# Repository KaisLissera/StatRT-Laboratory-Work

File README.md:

# Stat_RT_Laboratory_Work
 Updating of equipment for laboratory work on statistical radiotechnics

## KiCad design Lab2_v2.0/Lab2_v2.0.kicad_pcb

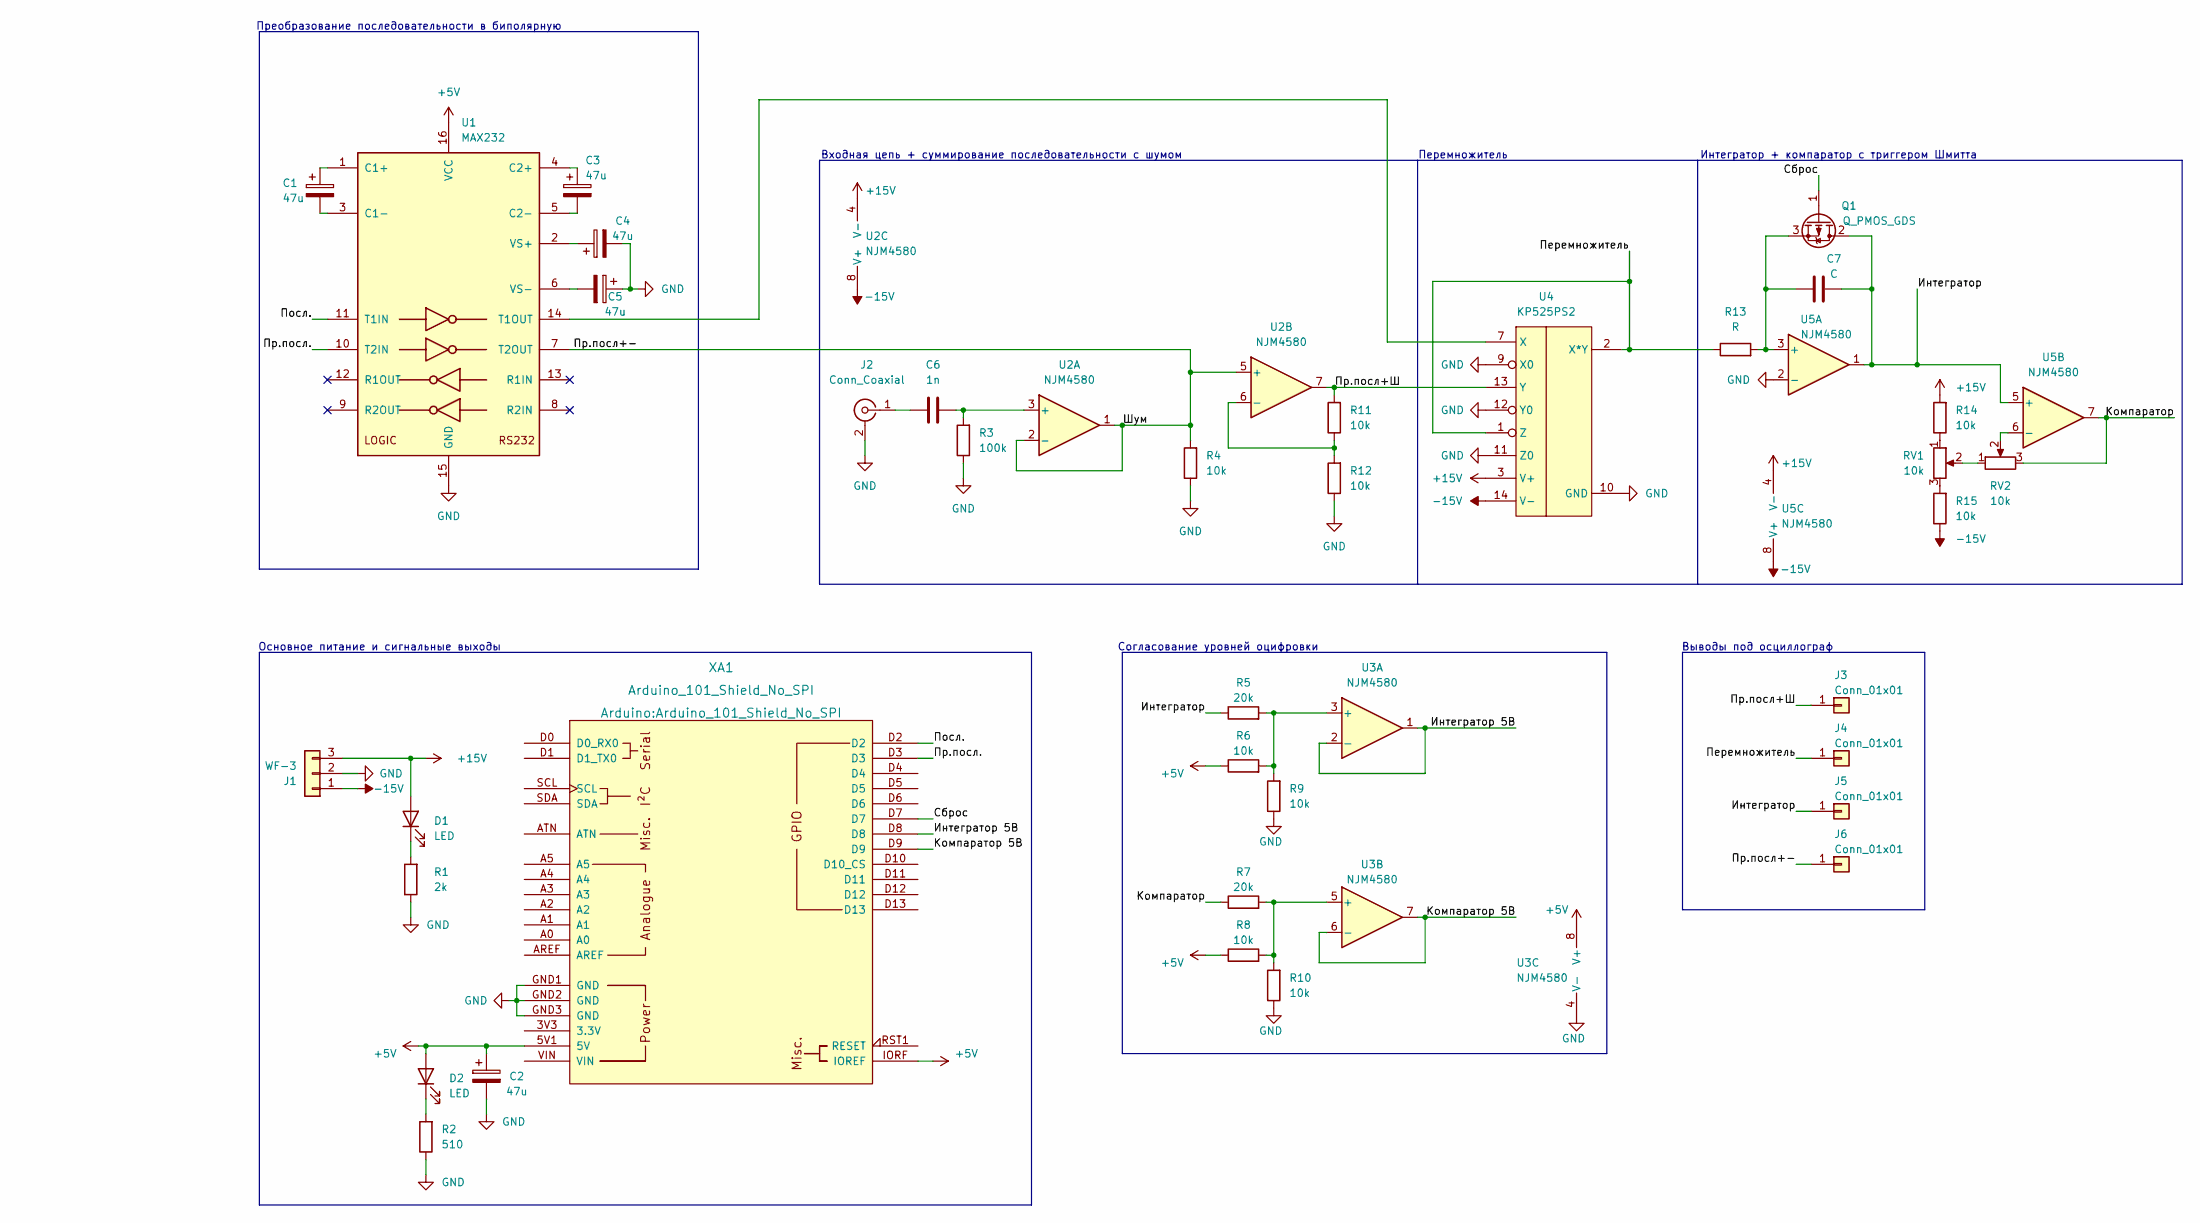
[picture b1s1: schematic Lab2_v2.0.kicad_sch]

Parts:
C1, C2, C3, C4, C5: 47u; CP_EIA-3216-18_Kemet-A_Pad1.58x1.35mm_HandSolder
C6: 1n; C_0603_1608Metric_Pad1.08x0.95mm_HandSolder
C7: C; C_0603_1608Metric_Pad1.08x0.95mm_HandSolder
D1, D2: LED; LED_0603_1608Metric_Pad1.05x0.95mm_HandSolder
J1: WF-3; PinHeader_1x03_P2.54mm_Vertical
J2: Conn_Coaxial; BNC_TEConnectivity_1478204_Vertical
J3, J4, J5, J6: Conn_01x01; PinHeader_1x01_P2.54mm_Vertical
Q1: Q_PMOS_GDS; SOT-23
R1: 2k; R_0603_1608Metric_Pad0.98x0.95mm_HandSolder
R2: 510; R_0603_1608Metric_Pad0.98x0.95mm_HandSolder
R3: 100k; R_0603_1608Metric_Pad0.98x0.95mm_HandSolder
R4, R6, R8, R9, R10, R11, R12, R14, R15: 10k; R_0603_1608Metric_Pad0.98x0.95mm_HandSolder
R5, R7: 20k; R_0603_1608Metric_Pad0.98x0.95mm_HandSolder
R13: R; R_0603_1608Metric_Pad0.98x0.95mm_HandSolder
RV1, RV2: 10k; Potentiometer_Bourns_3266W_Vertical
U1: MAX232; DIP-16_W7.62mm
U2, U3, U5: NJM4580; SOIC-8_3.9x4.9mm_P1.27mm
U4: KP525PS2; DIP-14_W7.62mm
XA1: Arduino_101_Shield_No_SPI

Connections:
+5V: C2.1, D2.2 (A), R6.1, R8.1, U1.16 (VCC), U3.8 (V+), XA1.5V1 (5V), XA1.IORF (IOREF)
+15V: D1.2 (A), J1.3, R14.2, U2.4 (V-), U4.3 (V+), U5.4 (V-)
-15V: J1.1, R15.1, U2.8 (V+), U4.14 (V-), U5.8 (V+)
/Интегратор: C7.2, J5.1, Q1.2 (D), R5.1, U5.1, U5.5 (+)
/Интегратор 5В: U3.1, U3.2 (-), XA1.D8
/Компаратор: R7.1, RV2.3, U5.7
/Компаратор 5В: U3.6 (-), U3.7, XA1.D9
/Перемножитель: J4.1, R13.1, U4.1 (Z), U4.2 (X*Y)
/Посл.: U1.11 (T1IN), XA1.D2
/Пр.посл+-: J6.1, R4.2, U1.7 (T2OUT), U2.1, U2.2 (-), U2.5 (+)
/Пр.посл+Ш: J3.1, R11.2, U2.7, U4.13 (Y)
/Пр.посл.: U1.10 (T2IN), XA1.D3
/Сброс: Q1.1 (G), XA1.D7
GND: C2.2, C4.2, C5.1, J1.2, J2.2 (Ext), R1.1, R2.1, R3.1, R4.1, R9.1, R10.1, R12.1, U1.15 (GND), U3.4 (V-), U4.6, U4.9 (X0), U4.10 (GND), U4.11 (Z0), U4.12 (Y0), U5.2 (-), XA1.GND1 (GND), XA1.GND2 (GND), XA1.GND3 (GND)
unnamed: C1.1, U1.1 (C1+)
unnamed: C1.2, U1.3 (C1-)
unnamed: C3.1, U1.4 (C2+)
unnamed: C3.2, U1.5 (C2-)
unnamed: C4.1, U1.2 (VS+)
unnamed: C5.2, U1.6 (VS-)
unnamed: C6.1, J2.1 (In)
unnamed: C6.2, R3.2, U2.3 (+)
unnamed: C7.1, Q1.3 (S), R13.2, U5.3 (+)
unnamed: D1.1 (K), R1.2
unnamed: D2.1 (K), R2.2
unnamed: R5.2, R6.2, R9.2, U3.3 (+)
unnamed: R7.2, R8.2, R10.2, U3.5 (+)
unnamed: R11.1, R12.2, U2.6 (-)
unnamed: R14.1, RV1.1
unnamed: R15.2, RV1.3
unnamed: RV1.2, RV2.1
unnamed: RV2.2, U5.6 (-)
unnamed: U1.14 (T1OUT), U4.7 (X)

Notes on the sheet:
Входная цепь + суммирование последовательности с шумом
Интегратор + компаратор с триггером Шмитта
Преобразование последовательности в биполярную
Основное питание и сигнальные выходы
Выводы под осциллограф
Согласование уровней оцифровки
Перемножитель

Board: 2 copper layers, 39 parts (0 on the bottom side), 33 nets, no tracks yet.

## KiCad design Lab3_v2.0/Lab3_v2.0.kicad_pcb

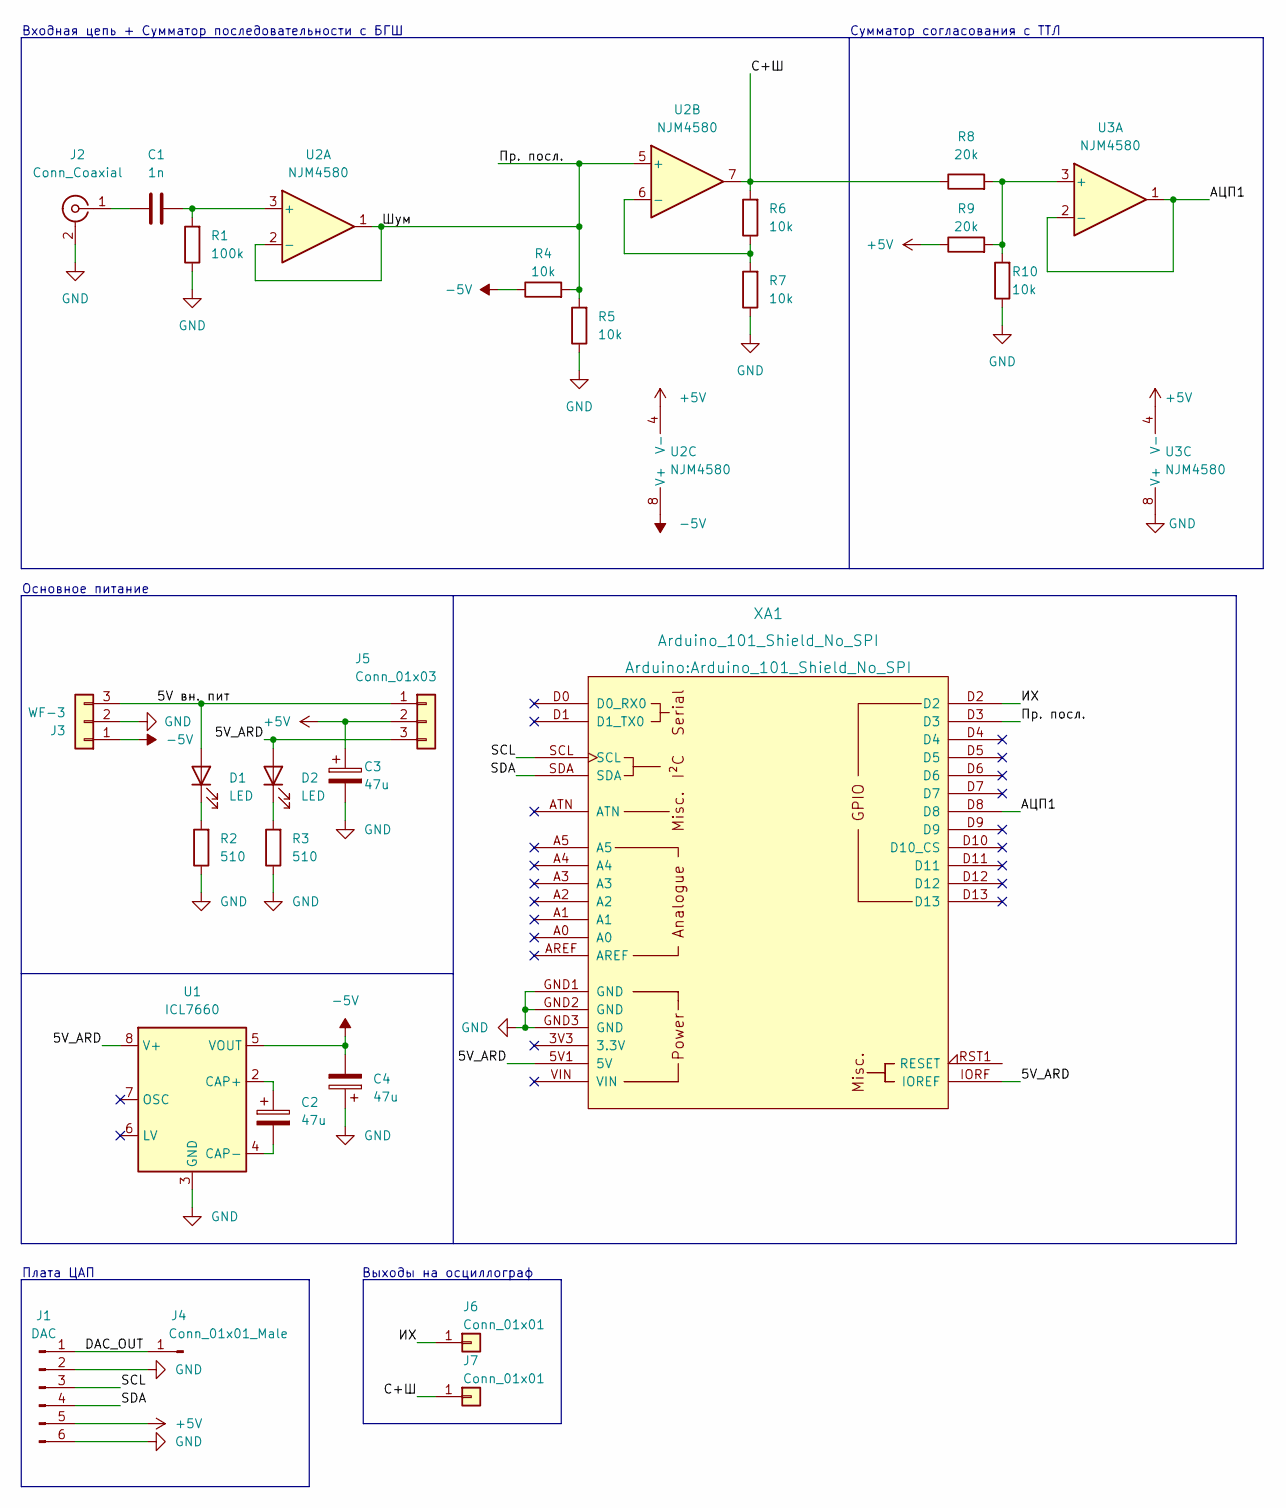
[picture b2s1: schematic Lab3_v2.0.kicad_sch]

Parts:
C1: 1n; C_0603_1608Metric_Pad1.08x0.95mm_HandSolder
C2, C3, C4: 47u; CP_EIA-3216-18_Kemet-A_Pad1.58x1.35mm_HandSolder
D1, D2: LED; D_0603_1608Metric_Pad1.05x0.95mm_HandSolder
J1: DAC; MCP4725
J2: Conn_Coaxial; BNC_TEConnectivity_1478204_Vertical
J3: WF-3; PinHeader_1x03_P2.54mm_Vertical
J4: Conn_01x01_Male; PinHeader_1x01_P2.54mm_Vertical
J5: Conn_01x03; PinHeader_1x03_P2.54mm_Vertical
J6, J7: Conn_01x01; PinHeader_1x01_P2.54mm_Vertical
R1: 100k; R_0603_1608Metric_Pad0.98x0.95mm_HandSolder
R2, R3: 510; R_0603_1608Metric_Pad0.98x0.95mm_HandSolder
R4, R5, R6, R7, R10: 10k; R_0603_1608Metric_Pad0.98x0.95mm_HandSolder
R8, R9: 20k; R_0603_1608Metric_Pad0.98x0.95mm_HandSolder
U1: ICL7660; SO-8_3.9x4.9mm_P1.27mm
U2, U3: NJM4580; SOIC-8_3.9x4.9mm_P1.27mm
XA1: Arduino_101_Shield_No_SPI

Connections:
+5V: C3.1, J1.5, J5.2, R9.1, U2.4 (V-), U3.4 (V-)
-5V: C4.2, J3.1, R4.1, U1.5 (VOUT), U2.8 (V+)
/5V вн. пит: D1.2 (A), J3.3, J5.1
/5V_ARD: D2.2 (A), J5.3, U1.8 (V+), XA1.5V1 (5V), XA1.IORF (IOREF)
/DAC_OUT: J1.1, J4.1
/SCL: J1.3, XA1.SCL
/SDA: J1.4, XA1.SDA
/АЦП1: U3.1, U3.2 (-), XA1.D8
/ИХ: J6.1, XA1.D2
/Пр. посл.: R4.2, R5.2, U2.1, U2.2 (-), U2.5 (+), XA1.D3
/С+Ш: J7.1, R6.2, R8.1, U2.7
GND: C3.2, C4.1, J1.2, J1.6, J2.2 (Ext), J3.2, R1.1, R2.1, R3.1, R5.1, R7.1, R10.1, U1.3 (GND), U3.8 (V+), XA1.GND1 (GND), XA1.GND2 (GND), XA1.GND3 (GND)
unnamed: C1.1, J2.1 (In)
unnamed: C1.2, R1.2, U2.3 (+)
unnamed: C2.1, U1.2 (CAP+)
unnamed: C2.2, U1.4 (CAP-)
unnamed: D1.1 (K), R2.2
unnamed: D2.1 (K), R3.2
unnamed: R6.1, R7.2, U2.6 (-)
unnamed: R8.2, R9.2, R10.2, U3.3 (+)

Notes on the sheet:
Основное питание
Входная цепь + Сумматор последовательности с БГШ
Сумматор согласования с ТТЛ
Плата ЦАП
Выходы на осциллограф

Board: 2 copper layers, 26 parts (0 on the bottom side), 17 nets, no tracks yet.

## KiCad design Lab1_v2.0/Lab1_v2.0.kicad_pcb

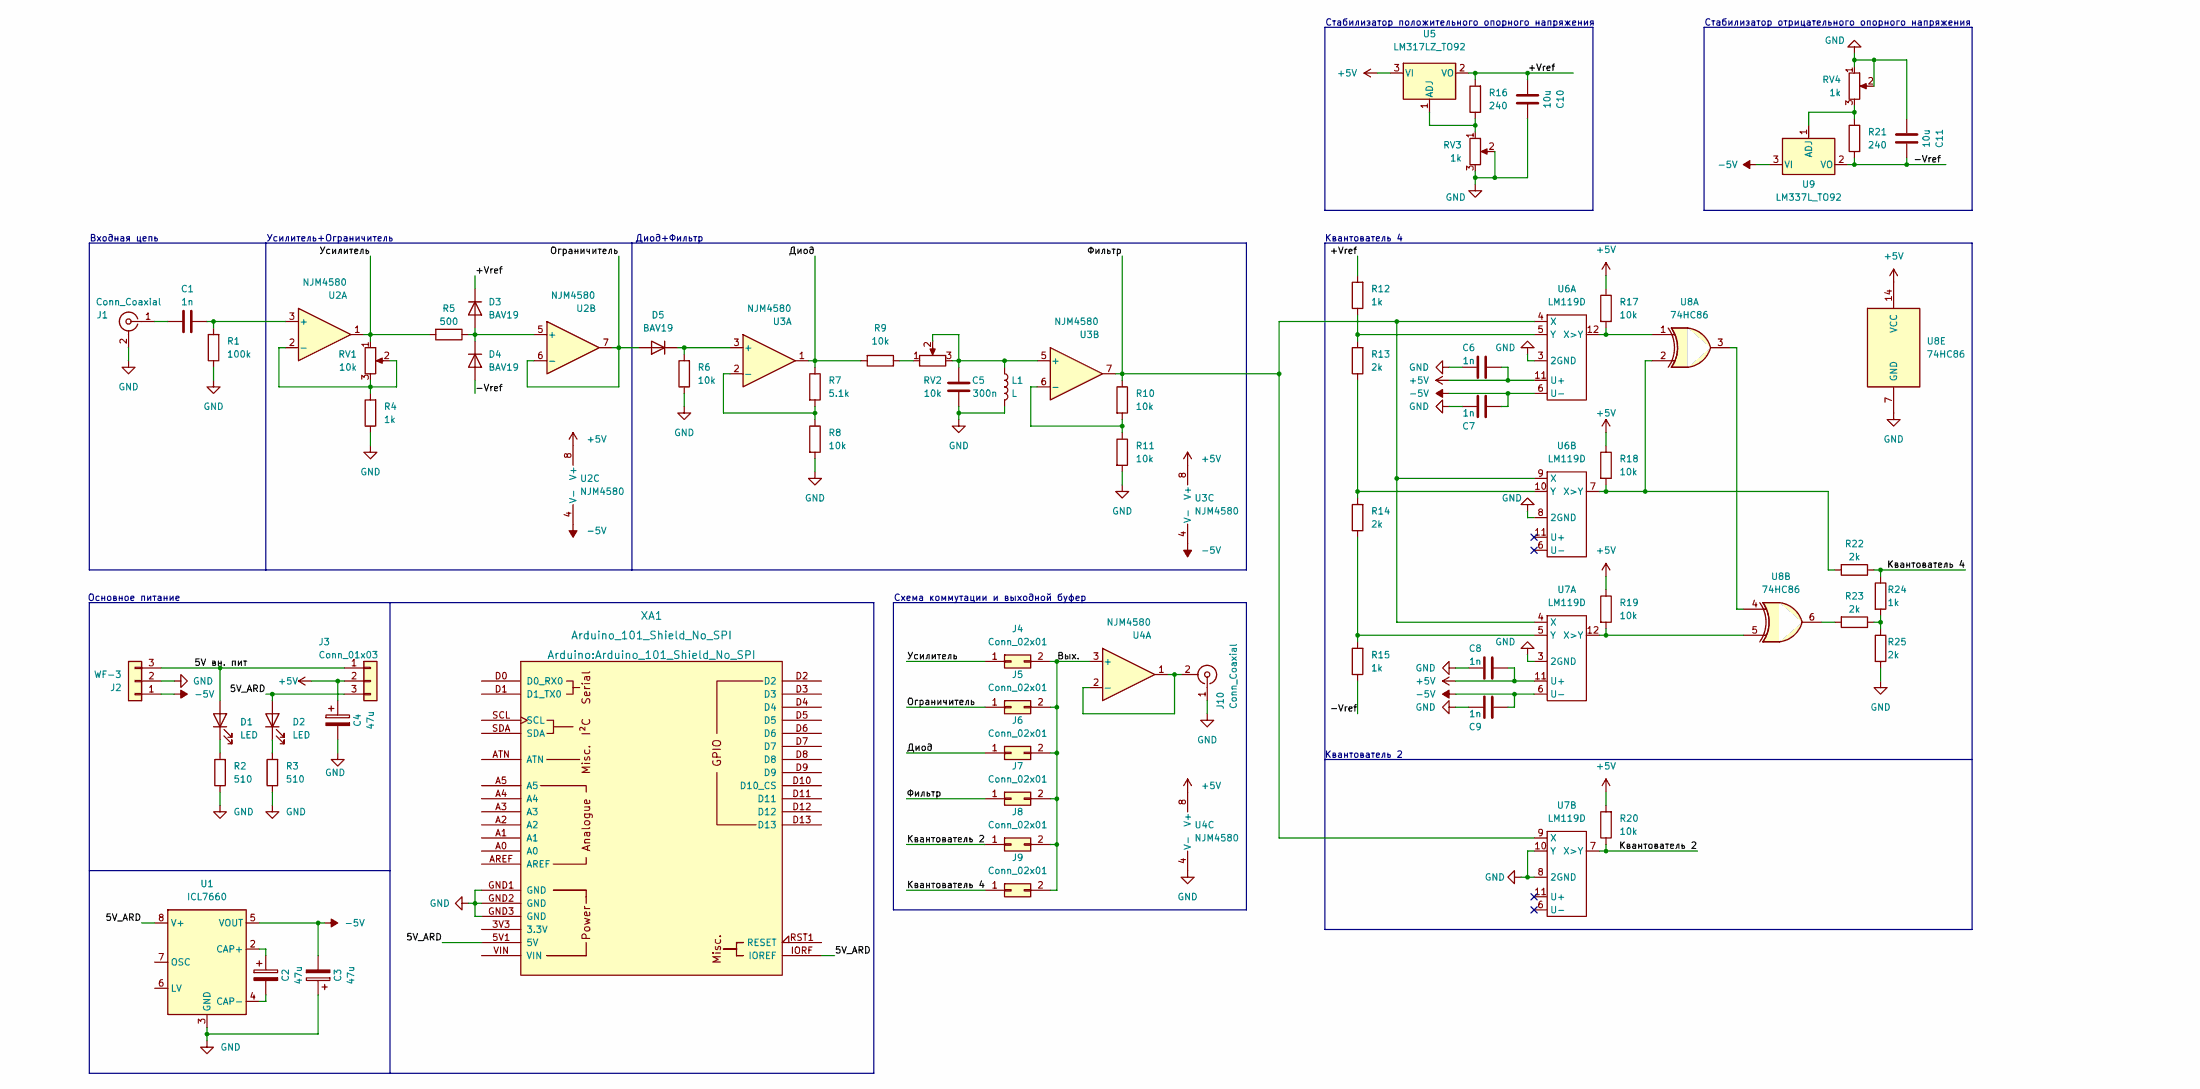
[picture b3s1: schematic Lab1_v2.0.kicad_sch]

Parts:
C1, C6, C7, C8, C9: 1n; C_0603_1608Metric_Pad1.08x0.95mm_HandSolder
C2, C3, C4: 47u; CP_EIA-3216-18_Kemet-A_Pad1.58x1.35mm_HandSolder
C5: 300n; C_0603_1608Metric_Pad1.08x0.95mm_HandSolder
C10, C11: 10u; C_0805_2012Metric_Pad1.18x1.45mm_HandSolder
D1, D2: LED; LED_0603_1608Metric_Pad1.05x0.95mm_HandSolder
D3, D4: BAV19; D_SOD-323
D5: BAV19; D_SOD-323_HandSoldering
J1, J10: Conn_Coaxial; BNC_TEConnectivity_1478204_Vertical
J2: WF-3; PinHeader_1x03_P2.54mm_Vertical
J3: Conn_01x03; PinHeader_1x03_P2.54mm_Vertical
J4, J5, J6, J7, J8, J9: Conn_02x01; PinHeader_2x01_P2.54mm_Vertical
L1: L; L_Radial_D7.5mm_P5.00mm_Fastron_07P
R1: 100k; R_0603_1608Metric_Pad0.98x0.95mm_HandSolder
R2, R3: 510; R_0603_1608Metric_Pad0.98x0.95mm_HandSolder
R4, R12, R15, R24: 1k; R_0603_1608Metric_Pad0.98x0.95mm_HandSolder
R5: 500; R_0603_1608Metric_Pad0.98x0.95mm_HandSolder
R6, R8, R9, R10, R11, R17, R18, R19, R20: 10k; R_0603_1608Metric_Pad0.98x0.95mm_HandSolder
R7: 5.1k; R_0603_1608Metric_Pad0.98x0.95mm_HandSolder
R13, R14, R22, R23, R25: 2k; R_0603_1608Metric_Pad0.98x0.95mm_HandSolder
R16, R21: 240; R_0603_1608Metric_Pad0.98x0.95mm_HandSolder
RV1, RV2: 10k; Potentiometer_Bourns_3266W_Vertical
RV3, RV4: 1k; Potentiometer_Bourns_3266W_Vertical
U1: ICL7660; SO-8_3.9x4.9mm_P1.27mm
U2, U3, U4: NJM4580; SOIC-8_3.9x4.9mm_P1.27mm
U5: LM317LZ_TO92; TO-92_Inline
U6, U7: LM119D; SOIC-14_3.9x8.7mm_P1.27mm
U8: 74HC86; SOIC-14_3.9x8.7mm_P1.27mm
U9: LM337L_TO92; TO-92_Inline
XA1: Arduino_101_Shield_No_SPI

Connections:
+5V: C4.1, C6.1, C8.1, J3.2, R17.1, R18.1, R19.1, R20.2, U2.8 (V+), U3.8 (V+), U4.8 (V+), U5.3 (VI), U6.11 (U+), U7.11 (U+), U8.14 (VCC)
-5V: C3.2, C7.2, C9.2, J2.1, U1.5 (VOUT), U2.4 (V-), U3.4 (V-), U6.6 (U-), U7.6 (U-), U9.3 (VI)
/5V вн. пит: D1.2 (A), J2.3, J3.1
/5V_ARD: D2.2 (A), J3.3, U1.8 (V+), XA1.5V1 (5V), XA1.IORF (IOREF)
/+Vref: C10.1, D3.1 (K), R12.2, R16.2, U5.2 (VO)
/-Vref: C11.2, D4.2 (A), R15.1, R21.1, U9.2 (VO)
/Вых.: J4.2, J5.2, J6.2, J7.2, J8.2, J9.2, U4.3 (+)
/Диод: J6.1, R7.1, R9.2, U3.1
/Квантователь 2: J8.1, R20.1, U7.7 (X>Y)
/Квантователь 4: J9.1, R22.1, R24.1
/Ограничитель: D5.2 (A), J5.1, U2.6 (-), U2.7
/Усилитель: J4.1, R5.2, RV1.1, U2.1
/Фильтр: J7.1, R10.1, U3.7, U6.4 (X), U6.9 (X), U7.4 (X), U7.9 (X)
GND: C3.1, C4.2, C5.1, C6.2, C7.1, C8.2, C9.1, C10.2, C11.1, J1.2 (Ext), J2.2, J10.1 (In), L1.2, R1.1, R2.1, R3.1, R4.1, R6.1, R8.2, R11.2, R25.2, RV3.2, RV3.3, RV4.1, RV4.2, U1.3 (GND), U4.4 (V-), U6.3 (2GND), U6.8 (2GND), U7.3 (2GND), U7.8 (2GND), U7.10 (Y), U8.7 (GND), XA1.GND1 (GND), XA1.GND2 (GND), XA1.GND3 (GND)
unnamed: C1.1, J1.1 (In)
unnamed: C1.2, R1.2, U2.3 (+)
unnamed: C2.1, U1.2 (CAP+)
unnamed: C2.2, U1.4 (CAP-)
unnamed: C5.2, L1.1, RV2.2, RV2.3, U3.5 (+)
unnamed: D1.1 (K), R2.2
unnamed: D2.1 (K), R3.2
unnamed: D3.2 (A), D4.1 (K), R5.1, U2.5 (+)
unnamed: D5.1 (K), R6.2, U3.3 (+)
unnamed: J10.2 (Ext), U4.1, U4.2 (-)
unnamed: R4.2, RV1.2, RV1.3, U2.2 (-)
unnamed: R7.2, R8.1, U3.2 (-)
unnamed: R9.1, RV2.1
unnamed: R10.2, R11.1, U3.6 (-)
unnamed: R12.1, R13.2, U6.5 (Y)
unnamed: R13.1, R14.2, U6.10 (Y)
unnamed: R14.1, R15.2, U7.5 (Y)
unnamed: R16.1, RV3.1, U5.1 (ADJ)
unnamed: R17.2, U6.12 (X>Y), U8.1
unnamed: R18.2, R22.2, U6.7 (X>Y), U8.2
unnamed: R19.2, U7.12 (X>Y), U8.5
unnamed: R21.2, RV4.3, U9.1 (ADJ)
unnamed: R23.1, R24.2, R25.1
unnamed: R23.2, U8.6
unnamed: U8.3, U8.4

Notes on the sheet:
Стабилизатор отрицательного опорного напряжения
Схема коммутации и выходной буфер
Усилитель+Ограничитель
Диод+Фильтр
Входная цепь
Квантователь 2
Основное питание
Стабилизатор положительного опорного напряжения
Квантователь 4

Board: 2 copper layers, 66 parts (0 on the bottom side), 39 nets, no tracks yet.

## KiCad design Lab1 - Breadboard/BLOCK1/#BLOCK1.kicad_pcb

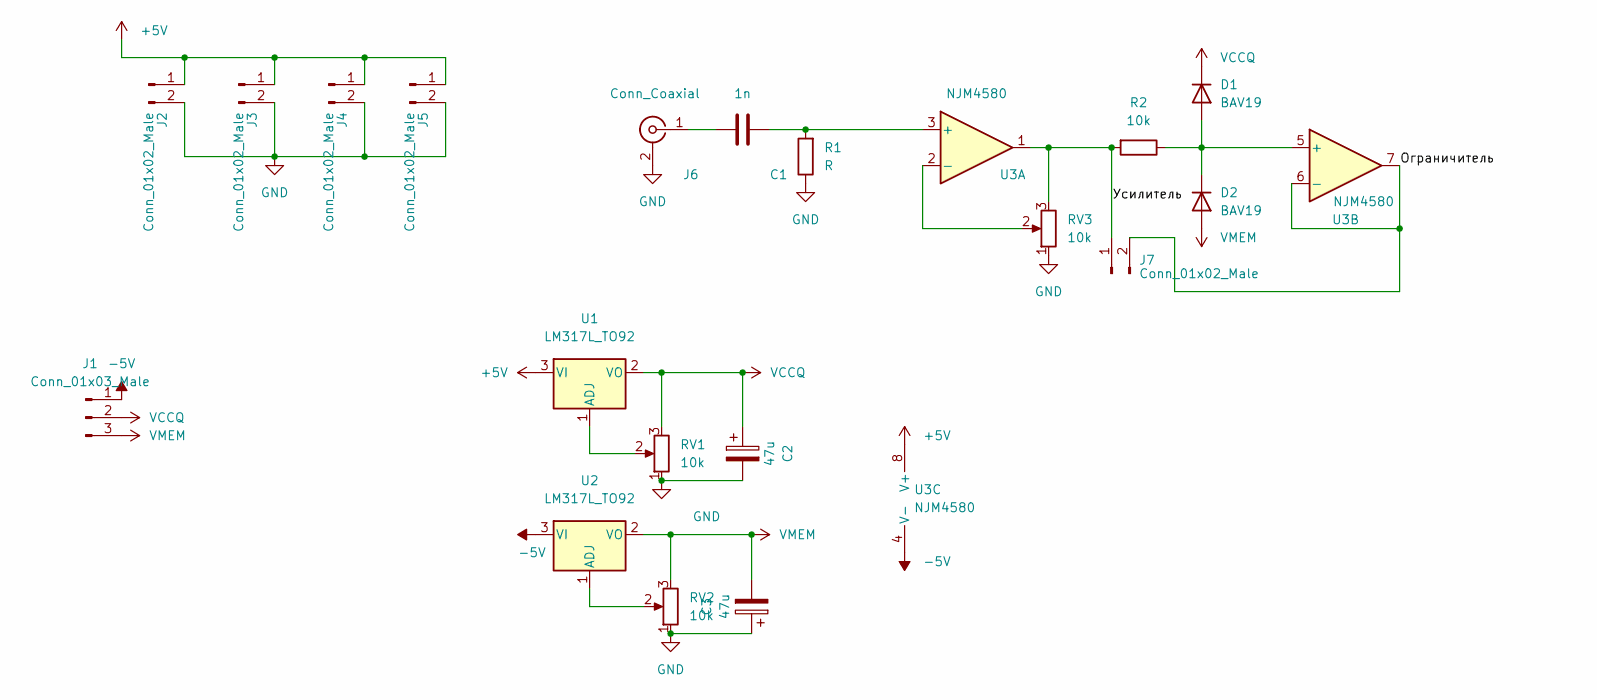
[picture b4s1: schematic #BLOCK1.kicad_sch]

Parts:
C1: 1n; C_1206_3216Metric_Pad1.33x1.80mm_HandSolder
C2, C3: 47u; C_1206_3216Metric_Pad1.33x1.80mm_HandSolder
D1, D2: BAV19; D_SOD-323
J1: Conn_01x03_Male; PinHeader_1x03_P2.54mm_Vertical
J2, J3, J4, J5, J7: Conn_01x02_Male; PinHeader_1x02_P2.54mm_Vertical
J6: Conn_Coaxial; BNC_TEConnectivity_1478204_Vertical
R1: R; R_1206_3216Metric_Pad1.30x1.75mm_HandSolder
R2: 10k; R_1206_3216Metric_Pad1.30x1.75mm_HandSolder
RV1, RV2, RV3: 10k; Potentiometer_Bourns_3266W_Vertical
U1, U2: LM317L_TO92; TO-92_Inline
U3: NJM4580; SOIC-8_3.9x4.9mm_P1.27mm

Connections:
+5V: J2.1, J3.1, J4.1, J5.1, U1.3 (VI), U3.8 (V+)
-5V: J1.1, U2.3 (VI), U3.4 (V-)
/Ограничитель: J7.2, U3.6 (-), U3.7
/Усилитель: J7.1, R2.2, RV3.3, U3.1
GND: C2.2, C3.1, J2.2, J3.2, J4.2, J5.2, J6.2 (Ext), R1.1, RV1.1, RV2.1, RV3.1
unnamed: C1.1, J6.1 (In)
unnamed: C1.2, R1.2, U3.3 (+)
unnamed: D1.2 (A), D2.1 (K), R2.1, U3.5 (+)
unnamed: RV1.2, U1.1 (ADJ)
unnamed: RV2.2, U2.1 (ADJ)
unnamed: RV3.2, U3.2 (-)
VCCQ: C2.1, D1.1 (K), J1.2, RV1.3, U1.2 (VO)
VMEM: C3.2, D2.2 (A), J1.3, RV2.3, U2.2 (VO)

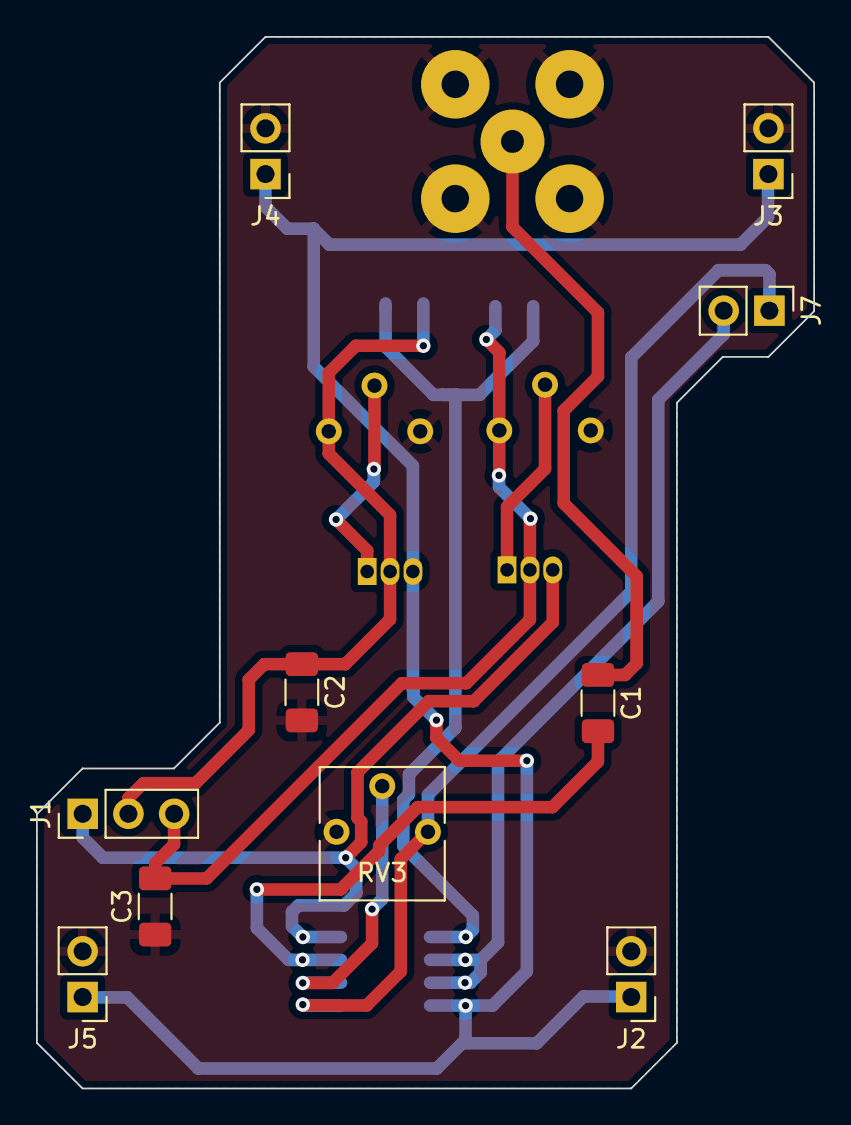
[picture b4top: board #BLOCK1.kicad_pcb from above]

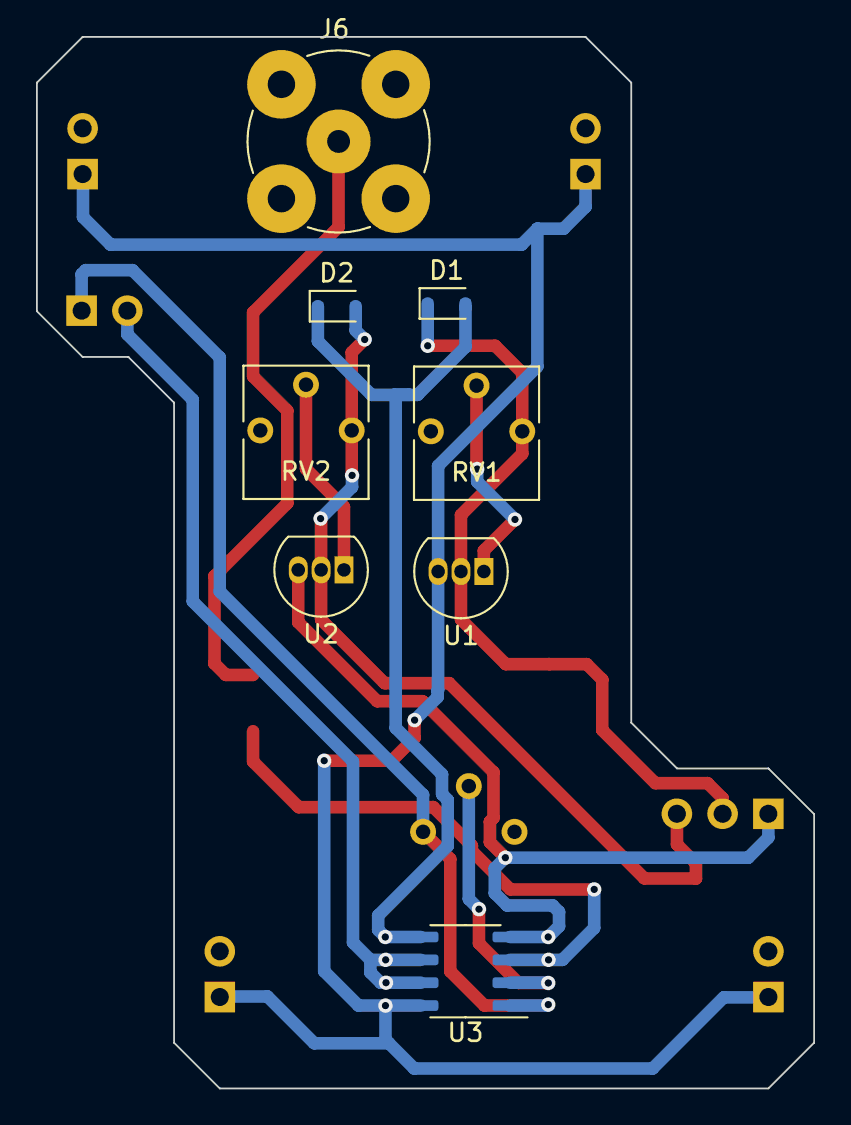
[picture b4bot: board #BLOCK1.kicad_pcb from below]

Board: 2 copper layers, 43.2 x 58.4 mm, 18 parts (8 on the bottom side), 13 nets.

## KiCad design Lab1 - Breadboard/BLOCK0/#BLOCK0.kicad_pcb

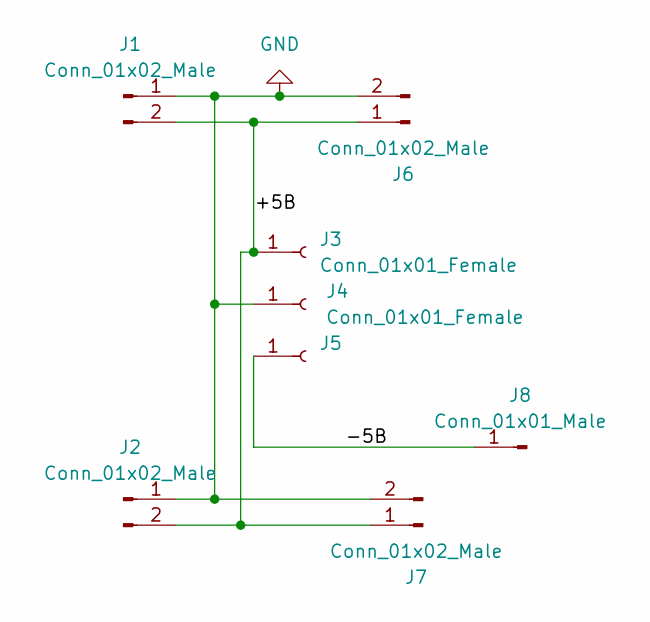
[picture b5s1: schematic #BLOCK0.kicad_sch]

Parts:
J1, J2, J6, J7: Conn_01x02_Male; PinHeader_1x02_P2.54mm_Vertical
J3, J4: Conn_01x01_Female; Banana_Jack_1Pin
J5: (no value)
J8: Conn_01x01_Male; PinHeader_1x01_P2.54mm_Vertical

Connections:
/+5В: J1.2, J2.2, J3.1, J6.1, J7.1
/-5В: J5.1, J8.1
GND: J1.1, J2.1, J4.1, J6.2, J7.2

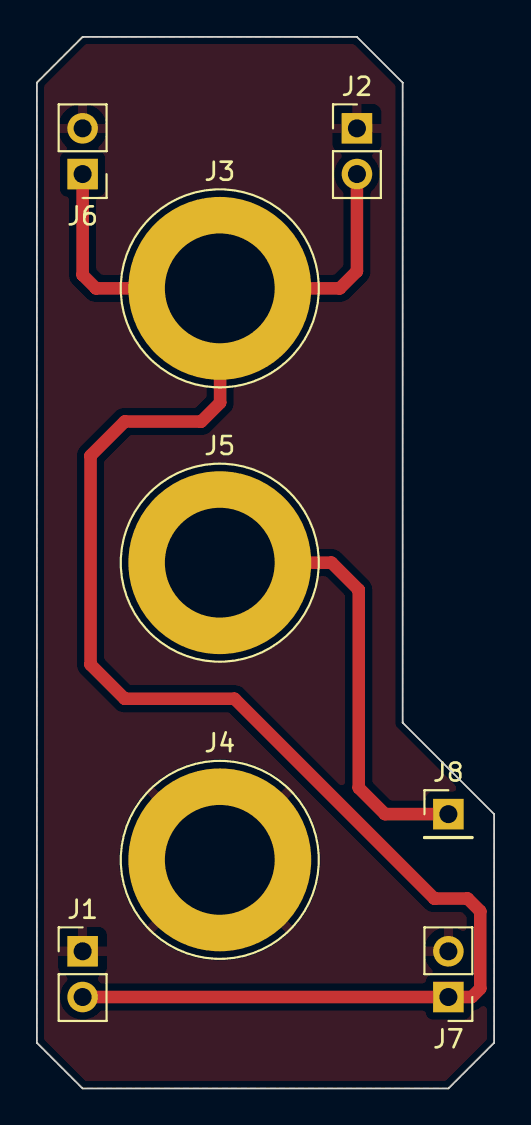
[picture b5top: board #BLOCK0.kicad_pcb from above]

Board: 2 copper layers, 25.4 x 58.4 mm, 8 parts (0 on the bottom side), 3 nets.

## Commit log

2022-05-27 Block0 & Block1
2022-09-25 Schematic rework
